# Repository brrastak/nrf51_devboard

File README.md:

Development board for the WT51822-S4AT module, that is based on the NRF51822 MCU.

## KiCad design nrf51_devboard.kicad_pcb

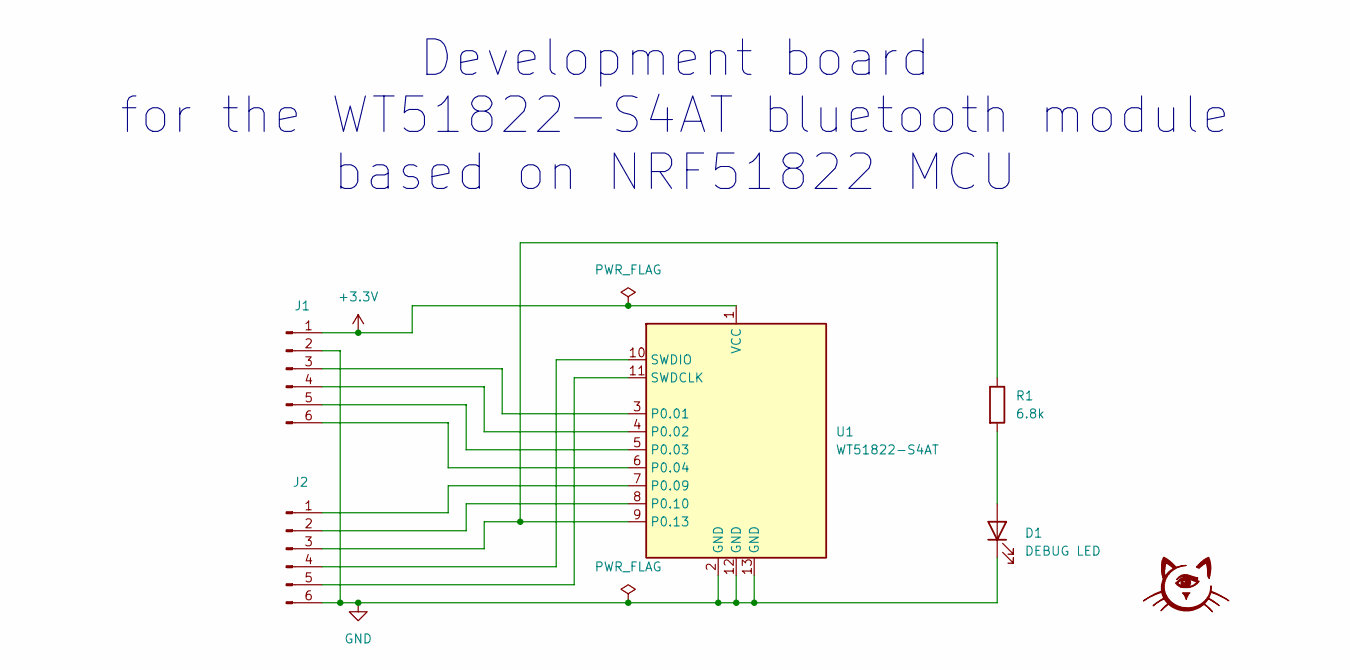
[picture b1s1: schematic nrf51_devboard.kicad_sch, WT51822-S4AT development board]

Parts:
D1: DEBUG LED; LED_0603_1608Metric_Pad1.05x0.95mm_HandSolder
G1: stamp
J1, J2: Conn_01x06_Male; PinHeader_1x06_P2.54mm_Vertical
R1: 6.8k; R_0603_1608Metric_Pad0.98x0.95mm_HandSolder
U1: WT51822-S4AT

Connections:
+3.3V: J1.1, U1.1 (VCC)
GND: D1.1 (K), J1.2, J2.6, U1.2 (GND), U1.12 (GND), U1.13 (GND)
unnamed: D1.2 (A), R1.2
unnamed: J1.3, U1.3 (P0.01)
unnamed: J1.4, U1.4 (P0.02)
unnamed: J1.5, U1.5 (P0.03)
unnamed: J1.6, U1.6 (P0.04)
unnamed: J2.1, U1.7 (P0.09)
unnamed: J2.2, U1.8 (P0.10)
unnamed: J2.3, R1.1, U1.9 (P0.13)
unnamed: J2.4, U1.10 (SWDIO)
unnamed: J2.5, U1.11 (SWDCLK)

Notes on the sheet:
Development board for the WT51822-S4AT bluetooth module based on NRF51822 MCU

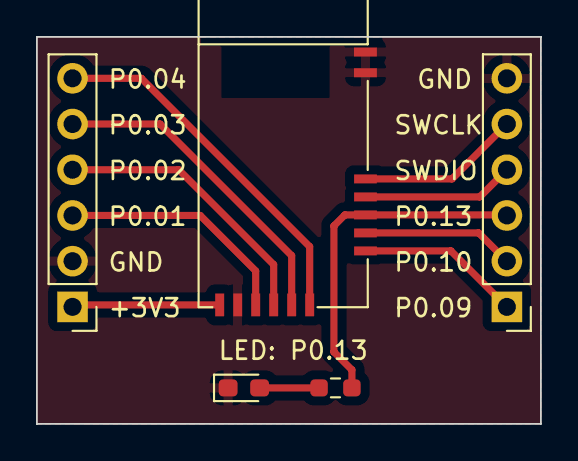
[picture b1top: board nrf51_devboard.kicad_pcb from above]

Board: 2 copper layers, 28.0 x 21.5 mm, 6 parts (1 on the bottom side), 12 nets.

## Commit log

2024-05-30 Create LICENSE
